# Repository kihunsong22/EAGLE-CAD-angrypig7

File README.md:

# EAGLE-CAD-angrypig7
EAGLE CAD files

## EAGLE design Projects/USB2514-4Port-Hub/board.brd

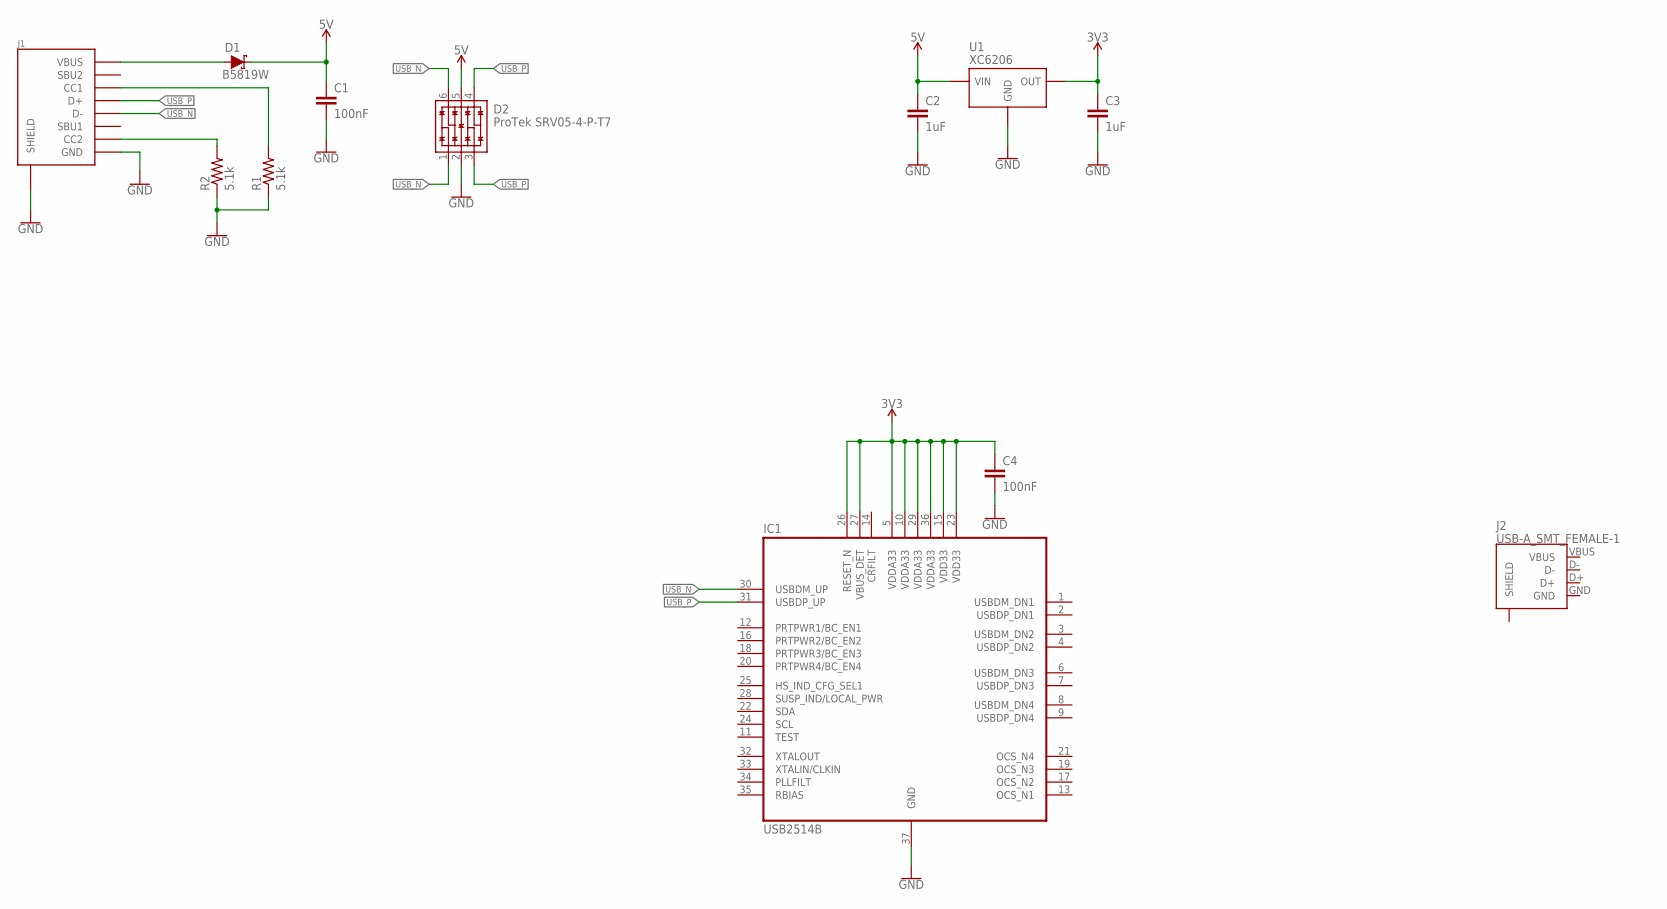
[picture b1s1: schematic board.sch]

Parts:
C1, C4: 100nF; C0402; LCSC C1525
C2, C3: 1uF; C0402; LCSC C52923
D1: B5819W; SOD-123; LCSC C8598
D2: ProTek SRV05-4-P-T7; SPT-23-6; LCSC C85364
IC1: USB2514B; QFN50P600X600X100-37T370N
J1: USB-TYPE-C-31-M-12; LCSC C165948
J2: USB-A_SMT_FEMALE-1; USB-A-FEMALE-2
R1, R2: 5.1k; R0402; LCSC C25905
U1: XC6206; SOT-23-3L; LCSC C5446

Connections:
3V3: C3.1, C4.1, IC1.5 (VDDA33), IC1.10 (VDDA33), IC1.15 (VDD33), IC1.23 (VDD33), IC1.26 (RESET_N), IC1.27 (VBUS_DET), IC1.29 (VDDA33), IC1.36 (VDDA33), U1.2 (OUT)
5V: C1.1, C2.1, D1.C, D2.5 (VCC), U1.3 (VIN)
5V_IN: D1.A, J1.VBUS1 (VBUS), J1.VBUS2 (VBUS)
GND: C1.2, C2.2, C3.2, C4.2, D2.2 (VSS), IC1.37 (GND), J1.GND1 (GND), J1.GND2 (GND), J1.SHLD-B1 (SHIELD), J1.SHLD-B2 (SHIELD), J1.SHLD-B3 (SHIELD), J1.SHLD-B4 (SHIELD), J1.SHLD-T1 (SHIELD), J1.SHLD-T2 (SHIELD), J1.SHLD-T3 (SHIELD), J1.SHLD-T4 (SHIELD), J2.GND, R1.1, R2.1, U1.1 (GND)
unnamed: J1.A5 (CC1), R1.2
unnamed: J1.B5 (CC2), R2.2
USB_N: D2.1 (IO1), D2.6 (IO4), IC1.30 (USBDM_UP), J1.A7 (D-), J1.B7 (D-)
USB_P: D2.3 (IO2), D2.4 (IO3), IC1.31 (USBDP_UP), J1.A6 (D+), J1.B6 (D+)
VBUS: J2.VBUS

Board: 2 copper layers, 12 parts (0 on the bottom side), 8 nets, no tracks yet.

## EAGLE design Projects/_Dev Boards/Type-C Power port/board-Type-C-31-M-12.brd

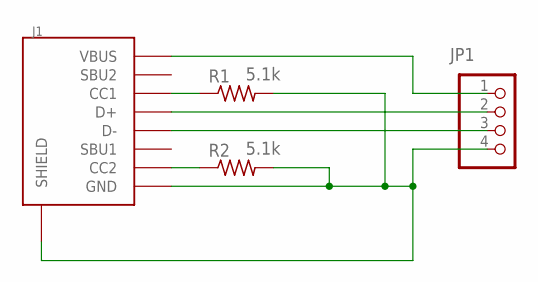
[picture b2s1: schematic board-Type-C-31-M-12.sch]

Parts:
J1: USB-TYPE-C-31-M-12
JP1: PINHD-1X4; 1X04
R1, R2: 5.1k; R0603

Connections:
GND: J1.GND1 (GND), J1.GND2 (GND), J1.SHLD-B1 (SHIELD), J1.SHLD-B2 (SHIELD), J1.SHLD-B3 (SHIELD), J1.SHLD-B4 (SHIELD), J1.SHLD-T1 (SHIELD), J1.SHLD-T2 (SHIELD), J1.SHLD-T3 (SHIELD), J1.SHLD-T4 (SHIELD), JP1.4, R1.2, R2.2
unnamed: J1.A6 (D+), J1.B6 (D+), JP1.2
unnamed: J1.A7 (D-), J1.B7 (D-), JP1.3
unnamed: J1.A5 (CC1), R1.1
unnamed: J1.B5 (CC2), R2.1
VBUS: J1.VBUS1 (VBUS), J1.VBUS2 (VBUS), JP1.1

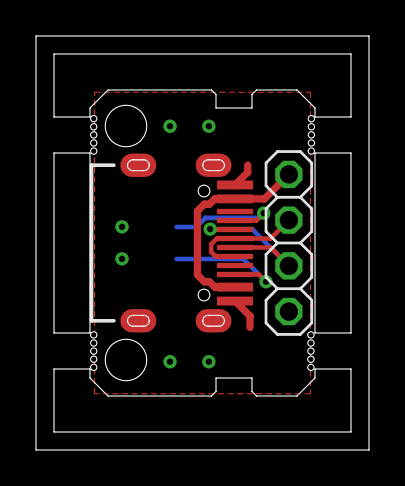
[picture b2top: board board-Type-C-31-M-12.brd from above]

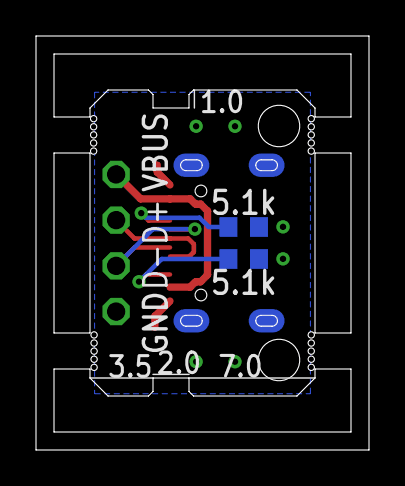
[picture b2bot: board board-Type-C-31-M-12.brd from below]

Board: 2 copper layers, 18.5 x 23.0 mm, 4 parts (2 on the bottom side), 6 nets.

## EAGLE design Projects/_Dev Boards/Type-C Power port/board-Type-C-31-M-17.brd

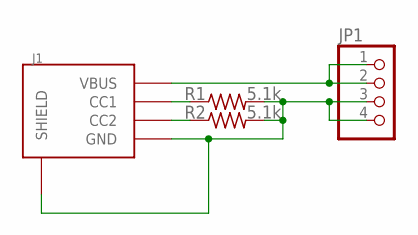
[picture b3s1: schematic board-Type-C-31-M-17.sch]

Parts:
J1: USB-TYPE-C-31-M-17
JP1: PINHD-1X4; 1X04
R1, R2: 5.1k; R0603

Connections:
GND: J1.GND, J1.GND_2 (GND), J1.SHLD-B1 (SHIELD), J1.SHLD-B2 (SHIELD), J1.SHLD-B3 (SHIELD), J1.SHLD-B4 (SHIELD), J1.SHLD-T1 (SHIELD), J1.SHLD-T2 (SHIELD), J1.SHLD-T3 (SHIELD), J1.SHLD-T4 (SHIELD), JP1.3, JP1.4, R1.2, R2.2
unnamed: J1.CC1, R1.1
unnamed: J1.CC2, R2.1
VBUS: J1.VBUS, J1.VBUS_2 (VBUS), JP1.1, JP1.2

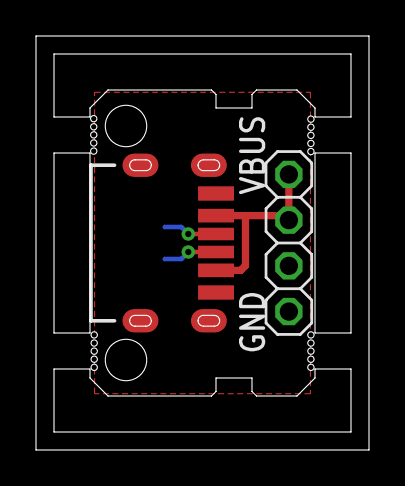
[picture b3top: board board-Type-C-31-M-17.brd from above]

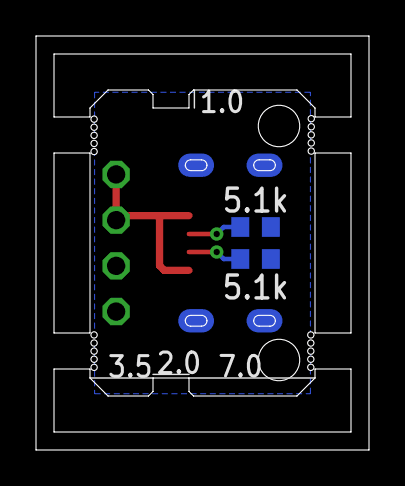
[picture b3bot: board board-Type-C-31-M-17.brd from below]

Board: 2 copper layers, 18.5 x 23.0 mm, 4 parts (2 on the bottom side), 4 nets.

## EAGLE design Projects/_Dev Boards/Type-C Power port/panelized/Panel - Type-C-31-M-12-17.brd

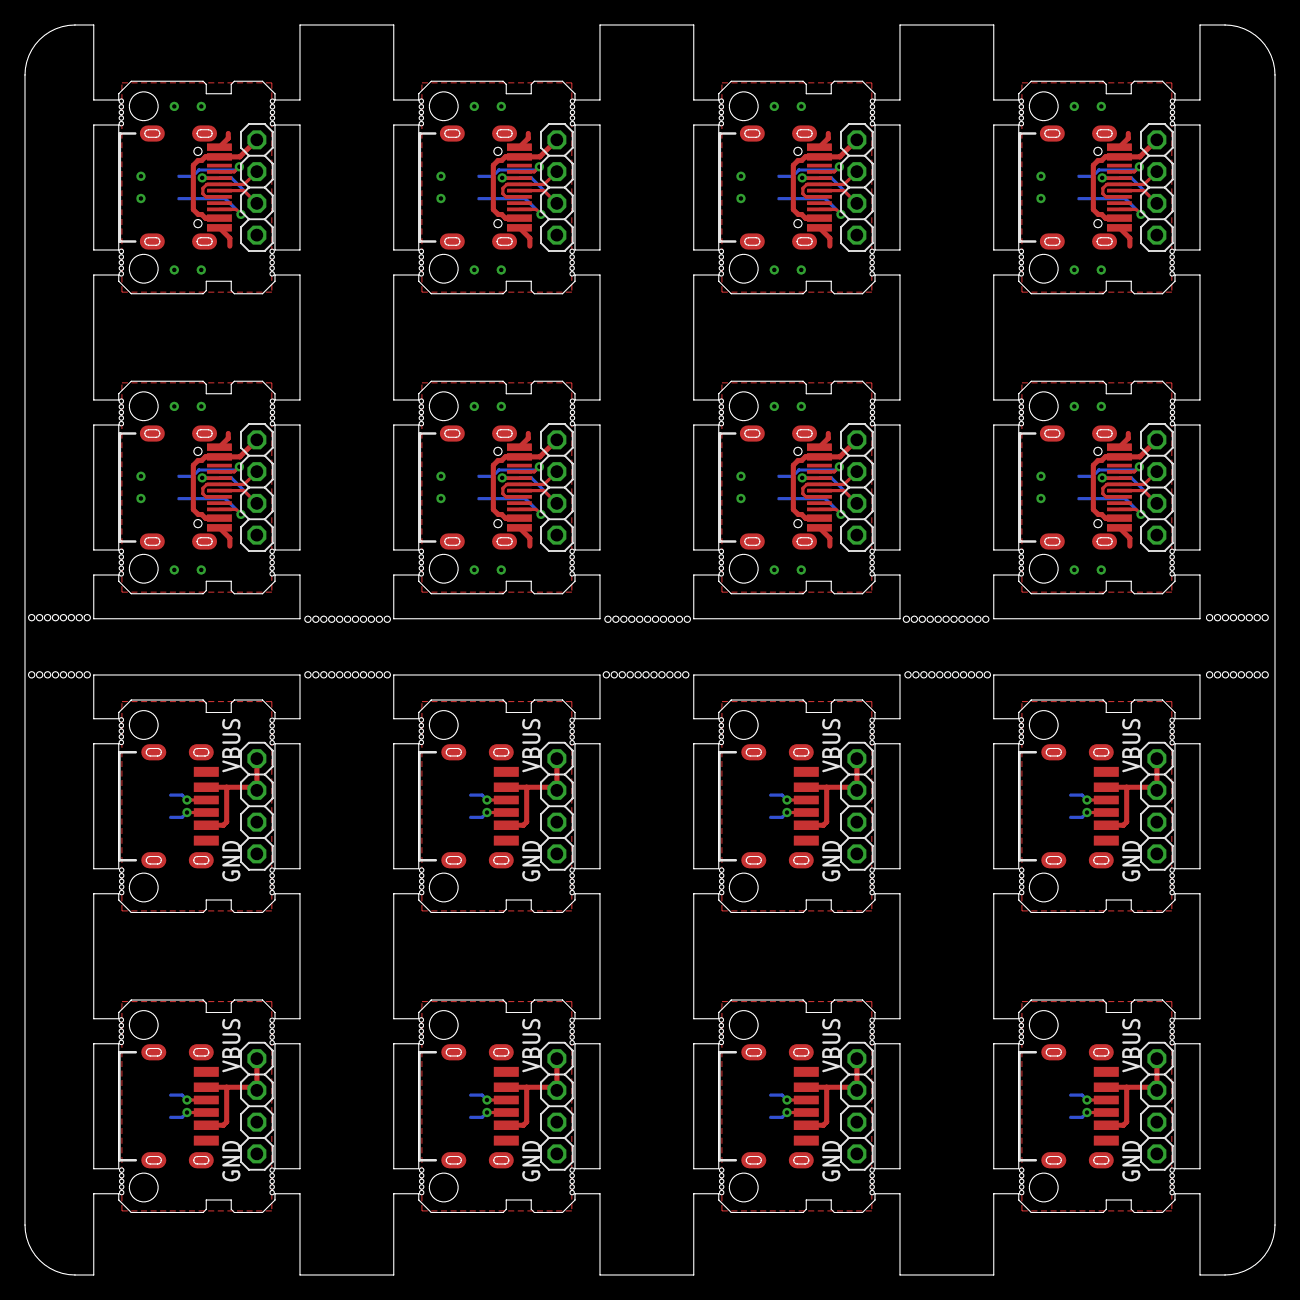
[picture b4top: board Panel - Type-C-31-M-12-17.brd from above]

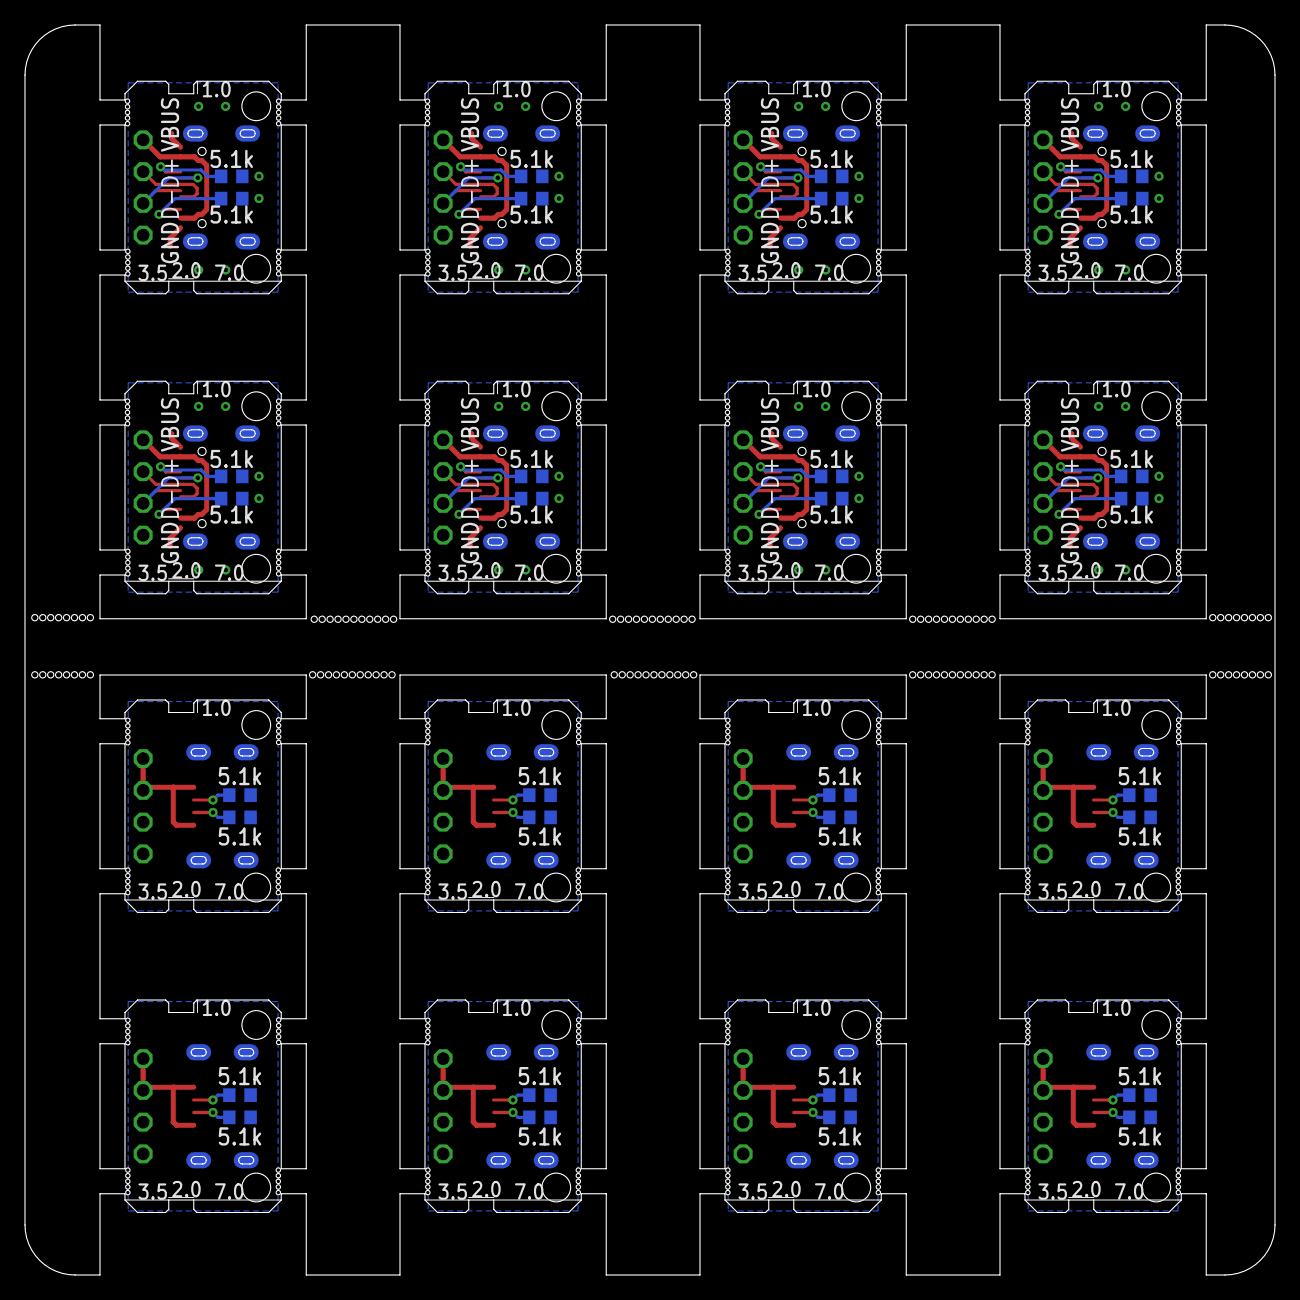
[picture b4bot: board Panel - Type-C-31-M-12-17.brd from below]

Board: 2 copper layers, 100.0 x 100.0 mm, 64 parts (32 on the bottom side), 80 nets.

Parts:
J1, J2, J3, J4, J5, J6, J7, J8: USB-TYPE-C-31-M-12
J9, J10, J11, J12, J13, J14, J15, J16: USB-TYPE-C-31-M-17
JP1, JP2, JP3, JP4, JP5, JP6, JP7, JP8, JP9, JP10, JP11, JP12, JP13, JP14, JP15, JP16: 1X04
R1, R2, R3, R4, R5, R6, R7, R8, R9, R10, R11, R12, R13, R14, R15, R16, R17, R18, R19, R20, R21, R22, R23, R24, R25, R26, R27, R28, R29, R30, R31, R32: 5.1k; R0603

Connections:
GND: J1.GND1, J1.GND2, J1.SHLD-B1, J1.SHLD-B2, J1.SHLD-B3, J1.SHLD-B4, J1.SHLD-T1, J1.SHLD-T2, J1.SHLD-T3, J1.SHLD-T4, JP1.4, R1.2, R2.2
GND1: J2.GND1, J2.GND2, J2.SHLD-B1, J2.SHLD-B2, J2.SHLD-B3, J2.SHLD-B4, J2.SHLD-T1, J2.SHLD-T2, J2.SHLD-T3, J2.SHLD-T4, JP2.4, R3.2, R4.2
GND2: J3.GND1, J3.GND2, J3.SHLD-B1, J3.SHLD-B2, J3.SHLD-B3, J3.SHLD-B4, J3.SHLD-T1, J3.SHLD-T2, J3.SHLD-T3, J3.SHLD-T4, JP3.4, R5.2, R6.2
GND3: J4.GND1, J4.GND2, J4.SHLD-B1, J4.SHLD-B2, J4.SHLD-B3, J4.SHLD-B4, J4.SHLD-T1, J4.SHLD-T2, J4.SHLD-T3, J4.SHLD-T4, JP4.4, R7.2, R8.2
GND4: J5.GND1, J5.GND2, J5.SHLD-B1, J5.SHLD-B2, J5.SHLD-B3, J5.SHLD-B4, J5.SHLD-T1, J5.SHLD-T2, J5.SHLD-T3, J5.SHLD-T4, JP5.4, R9.2, R10.2
GND5: J6.GND1, J6.GND2, J6.SHLD-B1, J6.SHLD-B2, J6.SHLD-B3, J6.SHLD-B4, J6.SHLD-T1, J6.SHLD-T2, J6.SHLD-T3, J6.SHLD-T4, JP6.4, R11.2, R12.2
GND6: J7.GND1, J7.GND2, J7.SHLD-B1, J7.SHLD-B2, J7.SHLD-B3, J7.SHLD-B4, J7.SHLD-T1, J7.SHLD-T2, J7.SHLD-T3, J7.SHLD-T4, JP7.4, R13.2, R14.2
GND7: J8.GND1, J8.GND2, J8.SHLD-B1, J8.SHLD-B2, J8.SHLD-B3, J8.SHLD-B4, J8.SHLD-T1, J8.SHLD-T2, J8.SHLD-T3, J8.SHLD-T4, JP8.4, R15.2, R16.2
GND8: J9.GND, J9.GND_2, J9.SHLD-B1, J9.SHLD-B2, J9.SHLD-B3, J9.SHLD-B4, J9.SHLD-T1, J9.SHLD-T2, J9.SHLD-T3, J9.SHLD-T4, JP9.3, JP9.4, R17.2, R18.2
GND9: J10.GND, J10.GND_2, J10.SHLD-B1, J10.SHLD-B2, J10.SHLD-B3, J10.SHLD-B4, J10.SHLD-T1, J10.SHLD-T2, J10.SHLD-T3, J10.SHLD-T4, JP10.3, JP10.4, R19.2, R20.2
GND10: J11.GND, J11.GND_2, J11.SHLD-B1, J11.SHLD-B2, J11.SHLD-B3, J11.SHLD-B4, J11.SHLD-T1, J11.SHLD-T2, J11.SHLD-T3, J11.SHLD-T4, JP11.3, JP11.4, R21.2, R22.2
GND11: J12.GND, J12.GND_2, J12.SHLD-B1, J12.SHLD-B2, J12.SHLD-B3, J12.SHLD-B4, J12.SHLD-T1, J12.SHLD-T2, J12.SHLD-T3, J12.SHLD-T4, JP12.3, JP12.4, R23.2, R24.2
GND12: J13.GND, J13.GND_2, J13.SHLD-B1, J13.SHLD-B2, J13.SHLD-B3, J13.SHLD-B4, J13.SHLD-T1, J13.SHLD-T2, J13.SHLD-T3, J13.SHLD-T4, JP13.3, JP13.4, R25.2, R26.2
GND13: J14.GND, J14.GND_2, J14.SHLD-B1, J14.SHLD-B2, J14.SHLD-B3, J14.SHLD-B4, J14.SHLD-T1, J14.SHLD-T2, J14.SHLD-T3, J14.SHLD-T4, JP14.3, JP14.4, R27.2, R28.2
GND14: J15.GND, J15.GND_2, J15.SHLD-B1, J15.SHLD-B2, J15.SHLD-B3, J15.SHLD-B4, J15.SHLD-T1, J15.SHLD-T2, J15.SHLD-T3, J15.SHLD-T4, JP15.3, JP15.4, R29.2, R30.2
GND15: J16.GND, J16.GND_2, J16.SHLD-B1, J16.SHLD-B2, J16.SHLD-B3, J16.SHLD-B4, J16.SHLD-T1, J16.SHLD-T2, J16.SHLD-T3, J16.SHLD-T4, JP16.3, JP16.4, R31.2, R32.2
unnamed: J2.A6, J2.B6, JP2.2
unnamed: J1.A6, J1.B6, JP1.2
unnamed: J1.A7, J1.B7, JP1.3
unnamed: J2.A7, J2.B7, JP2.3
unnamed: J1.A5, R1.1
unnamed: J1.B5, R2.1
unnamed: J2.A5, R3.1
unnamed: J2.B5, R4.1
unnamed: J3.A6, J3.B6, JP3.2
unnamed: J3.A7, J3.B7, JP3.3
unnamed: J3.A5, R5.1
unnamed: J3.B5, R6.1
unnamed: J4.A6, J4.B6, JP4.2
unnamed: J4.A7, J4.B7, JP4.3
unnamed: J4.A5, R7.1
unnamed: J4.B5, R8.1
unnamed: J5.A6, J5.B6, JP5.2
unnamed: J5.A7, J5.B7, JP5.3
unnamed: J5.A5, R9.1
unnamed: J5.B5, R10.1
unnamed: J6.A6, J6.B6, JP6.2
unnamed: J6.A7, J6.B7, JP6.3
unnamed: J6.A5, R11.1
unnamed: J6.B5, R12.1
unnamed: J7.A6, J7.B6, JP7.2
unnamed: J7.A7, J7.B7, JP7.3
unnamed: J7.A5, R13.1
unnamed: J7.B5, R14.1
unnamed: J8.A6, J8.B6, JP8.2
unnamed: J8.A7, J8.B7, JP8.3
unnamed: J8.A5, R15.1
unnamed: J8.B5, R16.1
unnamed: J9.CC1, R17.1
unnamed: J9.CC2, R18.1
unnamed: J10.CC1, R19.1
unnamed: J10.CC2, R20.1
unnamed: J11.CC1, R21.1
unnamed: J11.CC2, R22.1
unnamed: J12.CC1, R23.1
unnamed: J12.CC2, R24.1
unnamed: J13.CC1, R25.1
unnamed: J13.CC2, R26.1
unnamed: J14.CC1, R27.1
unnamed: J14.CC2, R28.1
unnamed: J15.CC1, R29.1
unnamed: J15.CC2, R30.1
unnamed: J16.CC1, R31.1
unnamed: J16.CC2, R32.1
VBUS: J1.VBUS1, J1.VBUS2, JP1.1
VBUS1: J2.VBUS1, J2.VBUS2, JP2.1
VBUS2: J3.VBUS1, J3.VBUS2, JP3.1
VBUS3: J4.VBUS1, J4.VBUS2, JP4.1
VBUS4: J5.VBUS1, J5.VBUS2, JP5.1
VBUS5: J6.VBUS1, J6.VBUS2, JP6.1
VBUS6: J7.VBUS1, J7.VBUS2, JP7.1
VBUS7: J8.VBUS1, J8.VBUS2, JP8.1
VBUS8: J9.VBUS, J9.VBUS_2, JP9.1, JP9.2
VBUS9: J10.VBUS, J10.VBUS_2, JP10.1, JP10.2
VBUS10: J11.VBUS, J11.VBUS_2, JP11.1, JP11.2
VBUS11: J12.VBUS, J12.VBUS_2, JP12.1, JP12.2
VBUS12: J13.VBUS, J13.VBUS_2, JP13.1, JP13.2
VBUS13: J14.VBUS, J14.VBUS_2, JP14.1, JP14.2
VBUS14: J15.VBUS, J15.VBUS_2, JP15.1, JP15.2
VBUS15: J16.VBUS, J16.VBUS_2, JP16.1, JP16.2

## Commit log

2020-04-16 gitignore
2020-04-16 moved from hardware_projects
2020-04-16 added IC libs used in LoRa shield
2020-05-03 added grid commands
2020-05-03 Type-C-31-M-12 part
2020-05-03 fixed Type-C connector slot hole error, legnthened M-12 connector SMD pad
2020-05-03 Type-C power port PCB panelized
2020-05-12 screw terminal blocks, pluggable teminal block
2020-05-15 breadboard PCB, cleanup
2020-05-15 eagle.scr is automatically applied at startup
2020-05-16 fixed soldermask errors with Type-C connector library
2020-05-16 updated Type-C power board
2020-05-17 script update
2020-05-17 library update: switches, ams1117, LED
2020-05-18 diode footprint update, new linear diode
2020-05-18 clocks
2020-05-20 startup script update, library update
2020-05-20 fixed orientation for JLCPCB PCBA
2020-05-24 SOICbite
2020-05-27 added PMOS, screw terminal error fix
2020-05-27 fixed error
2020-05-27 Type-C fixed footprint error
2020-06-01 added frames library
2020-06-01 new frames
2020-06-01 frame addlevel: must
2020-06-01 RCL C0402 size fix, parts rotated for JLCPCB assembly
2020-06-03 ESP-01
2020-06-04 made Type-C reversible
2020-06-04 added ESP8266EX, flash chip, fixed footprint error in AMS1117 SOT-89
2020-06-10 fixed C0402 footprint dimension
2020-06-13 con-pcb-slot
2020-06-18 JLCPCB PCBA exporter
2020-06-19 library update
2020-06-22 joystick switches
2020-06-22 joystick-ALPS RKJXV1224
2020-07-02 seperated MCUs
2020-07-02 JLCPCB SMTA exporter - oxullo
2020-07-02 STM32, SAMD21, nRF52832
2020-07-02 SX1276, LoRa modules
2020-07-07 STM32F103
2020-07-07 symbols library, 0402 cap footprint
2020-07-08 TCXO, crystals footprint
2020-07-09 removed attributes
2020-07-17 separated coaxial connectors
2020-07-18 copied sparkfun-jumpers lib
2020-07-21 DC-DC converters
2020-07-22 power inductors
2020-07-28 lib, TPS54331 design block
2020-07-29 SWF, U.FL connector
2020-07-30 seperated sensors, added SHT30
2020-07-31 Tag-Connect connector symbol
2020-07-31 TPS54331, SHT30 design block
2020-08-01 TC2030 pinmap RST->TDI
2020-08-07 3D packages
2020-08-07 SMA, SMB, SMC 3D package
2020-08-12 silkscreen b->t
2020-08-25 pinheads
2020-08-27 3D package
2020-09-09 JLCPCB DRC: 5->5.2mil clearance
2020-09-19 JLCPCB 2L design rules
2020-09-29 E22-900M22S
2020-09-29 SX1262 LoRa module symbol
2020-09-30 STM32 dev boards
2020-11-06 Type-C power port
2020-11-10 cleanup
2020-11-16 shrinked Type-C connector pads to prevent shorts
2020-11-30 new parts, error fixes
2020-12-05 fixed 3D packages
2020-12-06 fixed SMA package size
2020-12-13 fixed jumper footprint clearance issue
2020-12-13 added Sparkfun files
2021-01-05 seperated usb connectors
2021-01-11 feat: JLCPCB exporter suports manual part rotation via JLC_ROTATION attribute
2021-01-11 PCB antenna
2021-01-30 fixed pinout error
2021-03-23 USB2514B
2021-03-25 USB2514 hub project init
2021-08-09 test points
2021-08-09 TPS54331 design bock
2021-08-09 test jig coordinates
2021-08-11 design blocks - TPS54331 5V DC-DC, nRF52832
2021-08-12 logic NOT gate, Boards update
2021-08-13 update, fuses
2022-03-05 TH parts support
2023-01-01 fetch JLCPCB SMTA exporter from original repo
2023-04-11 rename script
2023-05-04 BAT54 series diodes
